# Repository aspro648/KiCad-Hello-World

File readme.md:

Introduction
------------

In programing, "Hello World" is the first program you write when you are learning a new language, so here it is for making printed circuit boards using open source [KiCad](http://kicad-pcb.org/).  This was for a one hour talk at [Teardown 2018](https://www.crowdsupply.com/teardown/portland-2018#schedule) in Portland, Oregon. Video of the presentation is on [Youtube](https://youtu.be/aWO80QdqLBQ).

Bill Of Materials
-----------------
  
- 1 ea. Perfect Purple PCB, https://oshpark.com/shared_projects/xqKKUJBu  
- 1 ea. Battery Holder, Keystone 3001, https://www.digikey.com/short/jmtqqd
- 1 ea. 3mm LED, https://www.digikey.com/short/jmtqj0
- 2 ea. 100 ohm resistors 1/4w, https://www.digikey.com/short/jmtqz7
- 1 ea. CR1220 battery, http://a.co/1LbhIgT
- 1 ea. tie tack (optional) http://a.co/7cv3B0N

Design Files
------------
This project is designed using Open Source [KiCad](http://kicad-pcb.org/). Design files are located in the [design_files](design_files/) folder.  

Firmware
--------
None

Assembly Instructions
---------------------
Check out Adafruit's excellent [soldering tutorial](https://learn.adafruit.com/adafruit-guide-excellent-soldering/).

License
-------
[Attribution-ShareAlike 3.0 United States (CC BY-SA 3.0 US)](https://creativecommons.org/licenses/by-sa/3.0/us/)

You are free to:

- Share — copy and redistribute the material in any medium or format
- Adapt — remix, transform, and build upon the material

Under the following terms:

- Attribution — You must give appropriate credit, provide a link to the license, and indicate if changes were made. You may do so in any reasonable manner, but not in any way that suggests the licensor endorses you or your use.
- ShareAlike — If you remix, transform, or build upon the material, you must distribute your contributions under the same license as the original.

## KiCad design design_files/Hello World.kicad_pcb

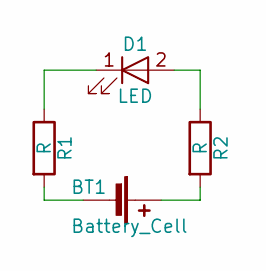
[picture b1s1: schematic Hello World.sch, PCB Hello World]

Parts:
BT1: Battery_Cell; Keystone_3001_1x12mm-CoinCell
D1: LED; LED_D3.0mm_Horizontal_O1.27mm_Z2.0mm
R1, R2: R; R_Axial_DIN0207_L6.3mm_D2.5mm_P7.62mm_Horizontal

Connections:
unnamed: BT1.1 (+), R2.2
unnamed: BT1.2 (-), R1.2
unnamed: D1.1 (K), R1.1
unnamed: D1.2 (A), R2.1

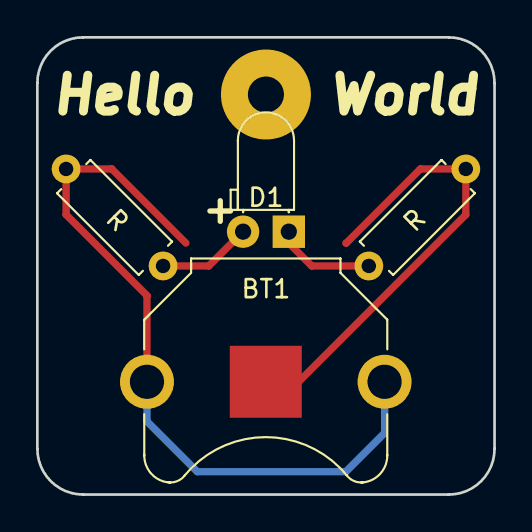
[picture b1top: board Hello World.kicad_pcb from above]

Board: 2 copper layers, 25.4 x 25.4 mm, 4 parts (0 on the bottom side), 4 nets.

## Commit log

2018-05-12 Initi commit
